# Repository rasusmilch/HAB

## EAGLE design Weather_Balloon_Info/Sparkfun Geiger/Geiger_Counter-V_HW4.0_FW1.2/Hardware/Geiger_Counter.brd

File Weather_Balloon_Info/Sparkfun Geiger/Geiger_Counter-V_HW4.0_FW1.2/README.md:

Geiger Counter
========================================
[
*Geiger Counter (SEN-11345)*](https://www.sparkfun.com/products/11345)

This USB powered Geiger Counter is equipped with an ATMega328 that can be programmed in-circuit. Out of the box, the board works
at 9600 bps over any serial terminal and generates random bits in reaction to background radiation.

Repository Contents
-------------------
* **/Firmware** - Firmware that ships on the Geiger Counter
* **/Hardware** - All Eagle design files (.brd, .sch)
* **/Production** - Test bed files and production panel files

Product Versions
----------------
* [SEN-11345](https://www.sparkfun.com/products/11345)- Version 2.1. Current.
* [SEN-10742](https://www.sparkfun.com/products/retired/10742)- Version 1.2-Retired. 

Version History
---------------
* [v21](https://github.com/sparkfun/Geiger_Counter/tree/HW_2.1_FW_2.1) GitHub version 2.1 files.
* [v12](https://github.com/sparkfun/Geiger_Counter/tree/v12) GitHub version 1.2 files. 

License Information
-------------------
The hardware is released under [Creative Commons ShareAlike 4.0 International](https://creativecommons.org/licenses/by-sa/4.0/).
The code is beerware; if you see me (or any other SparkFun employee) at the local, and you've found our code helpful, please buy us a round!

Distributed as-is; no warranty is given.

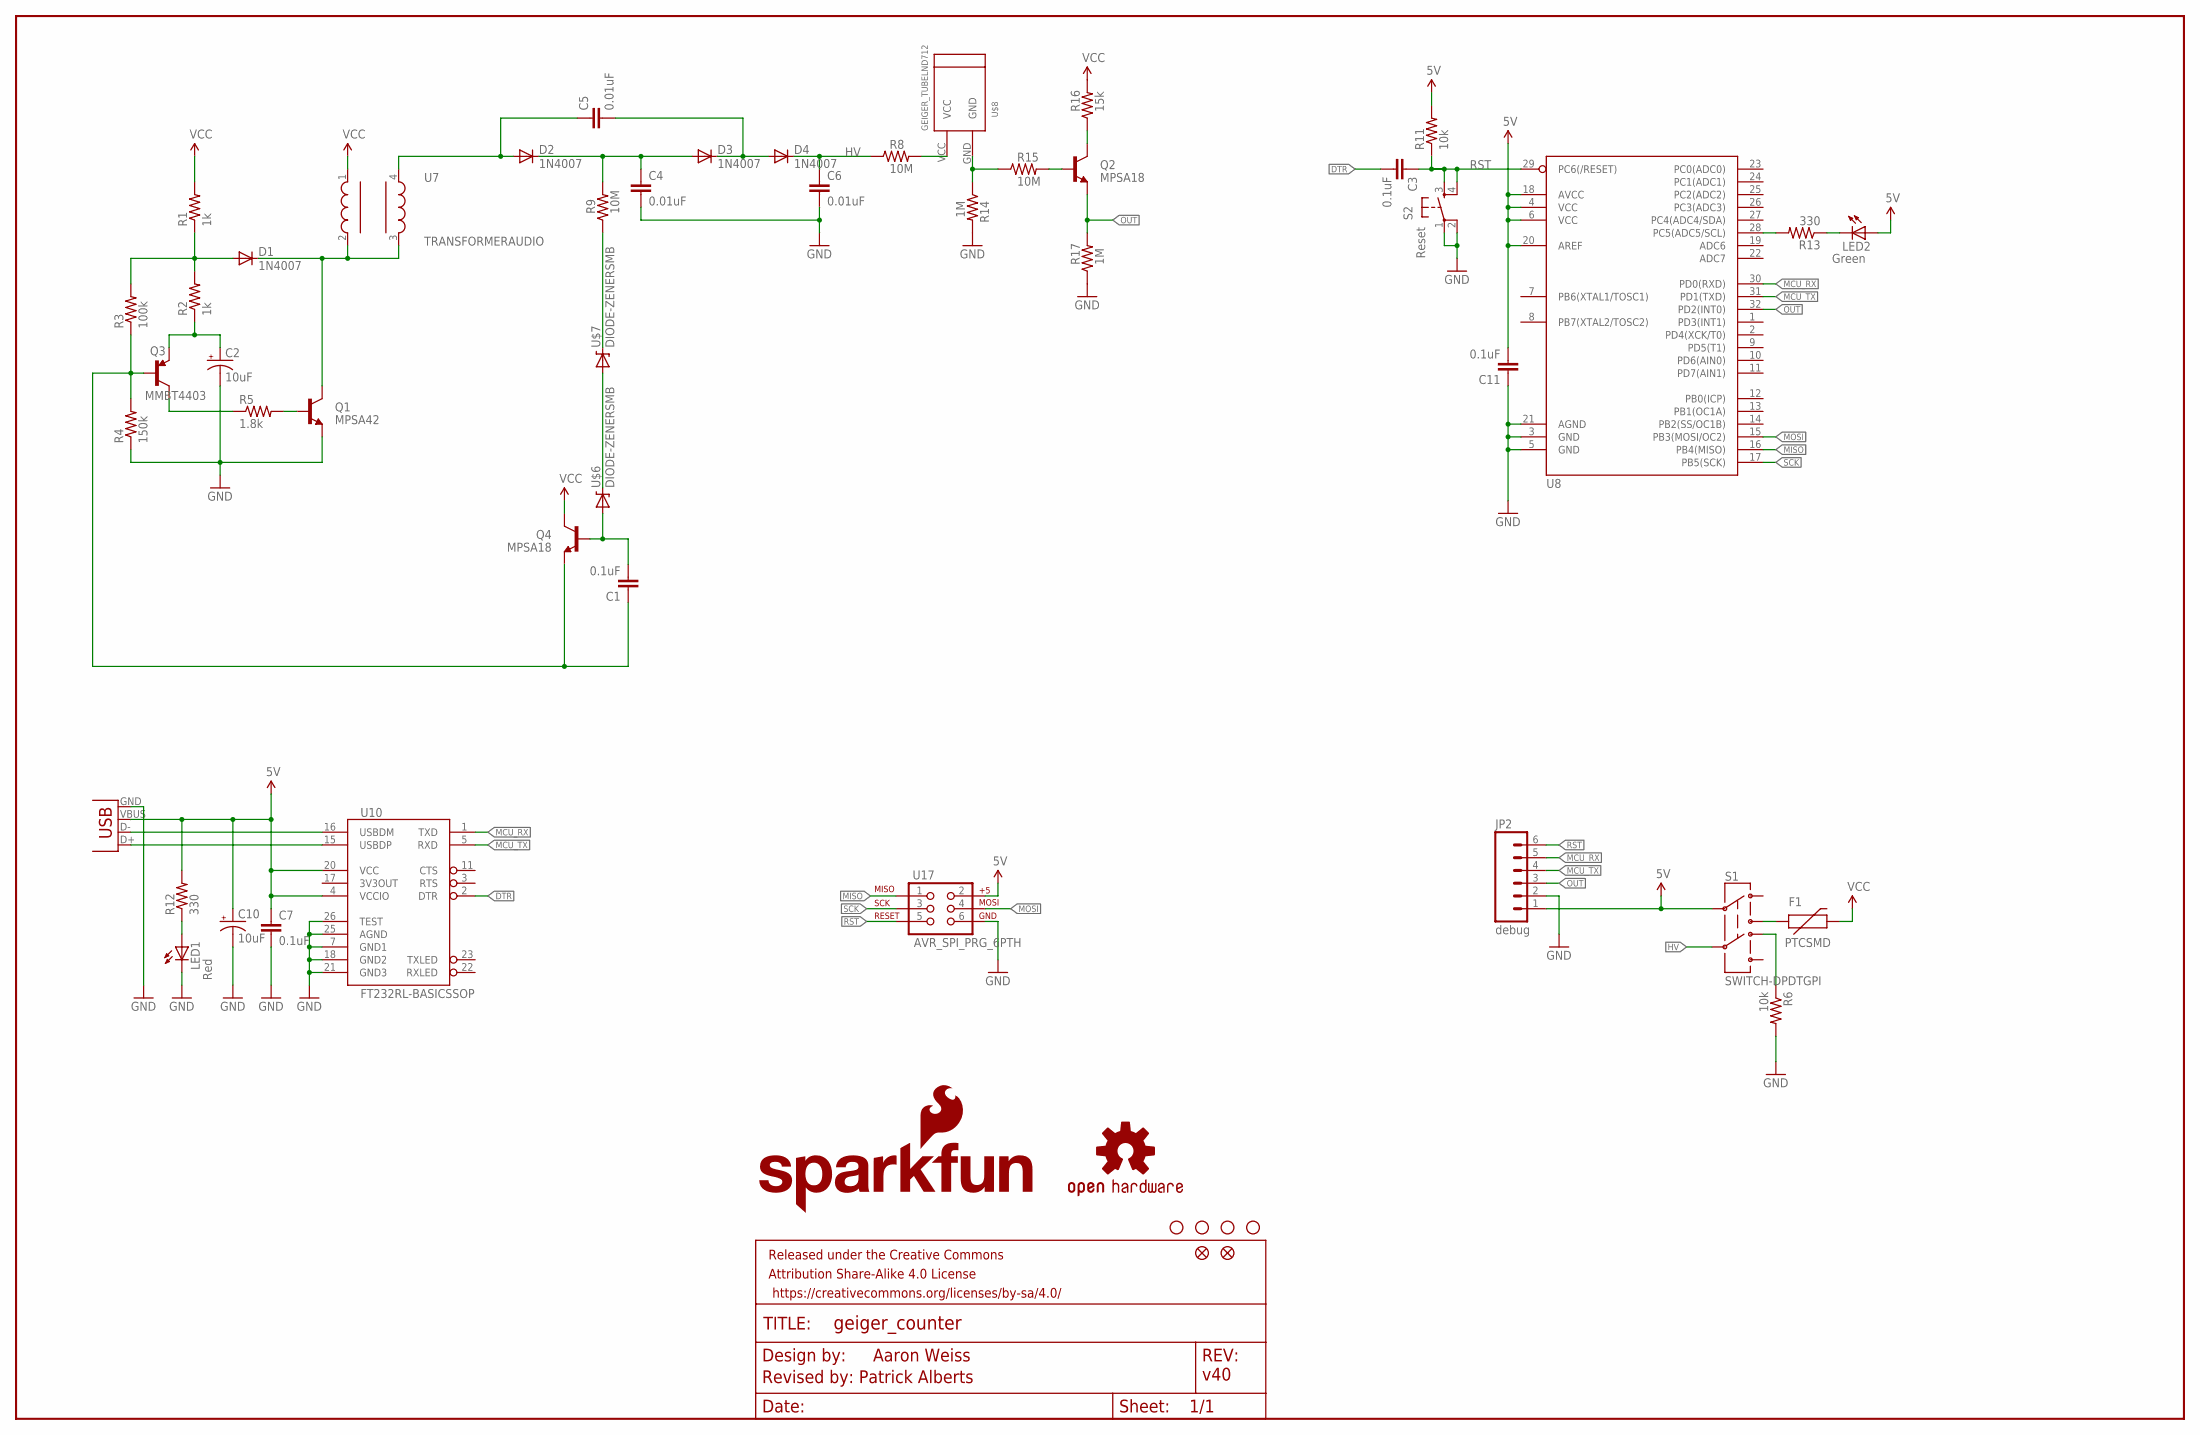
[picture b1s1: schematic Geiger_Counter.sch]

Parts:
C1, C3, C7, C11: 0.1uF; 0603-CAP
C2, C10: 10uF; EIA3216
C4, C5, C6: 0.01uF; CAP-PTH-LARGE
D1: 1N4007; DIODE-HV
D2, D3, D4: 1N4007; DIODE-1N4001
F1: PTCSMD; PTC-1206
FID1, FID2: FIDUCIAL1X2; FIDUCIAL-1X2
FRAME2: FRAME-LEDGER; CREATIVE_COMMONS
JP2: debug; 1X06
LED1: Red; LED-1206
LED2: Green; LED-1206
LOGO1: OSHW-LOGOM; OSHW-LOGO-M
LOGO2: SFE_LOGO_NAME_FLAME.1_INCH; SFE_LOGO_NAME_FLAME_.1
Q1: MPSA42; SOT23-3
Q2, Q4: MPSA18; TO-92
Q3: MMBT4403; SOT23-3
R1, R2: 1k; 0603-RES
R3: 100k; 0603-RES
R4: 150k; 0603-RES
R5: 1.8k; 0603-RES
R6: 10k; AXIAL-0.3
R8, R9, R15: 10M; AXIAL-0.3
R11: 10k; 0603-RES
R12: 330; 0603
R13: 330; 0603-RES
R14, R17: 1M; AXIAL-0.3
R16: 15k; AXIAL-0.3
S1: SWITCH-DPDTGPI; GPI-152-3013
S2: Reset; TACTILE_SWITCH_SMD
U7: TRANSFORMERAUDIO; TRANSFORMER
U8: ATMEGA328_SMT; TQFP32-08
U10: FT232RL-BASICSSOP; SSOP28DB
U17: AVR_SPI_PRG_6PTH; 2X3
U$1, U$2, U$3, U$4: STAND-OFF
U$6, U$7: DIODE-ZENERSMB; SMB-DIODE
U$8: GEIGER_TUBELND712; GEIGER_TUBE
X1: USBSMD; USB-MINIB

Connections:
5V: C7.1, C10.A (+), C11.2, JP2.1, LED2.A, R11.2, R12.2, S1.C@1 (2), U8.4 (VCC), U8.6 (VCC), U8.18 (AVCC), U8.20 (AREF), U10.4 (VCCIO), U10.20 (VCC), U17.2, X1.VBUS
DTR: C3.2, U10.2 (DTR)
GND: C2.C (-), C4.2, C6.2, C10.C (-), C11.1, JP2.2, LED1.C, Q1.2 (E), R4.1, R6.P$2 (2), R14.P$2 (2), R17.P$1 (1), S2.1, S2.2, U8.3 (GND), U8.5 (GND), U8.21 (AGND), U10.7 (GND1), U10.18 (GND2), U10.21 (GND3), U10.25 (AGND), U10.26 (TEST), U17.6, X1.GND
HV: C6.1, D4.C, R8.P$1 (1), S1.C@2 (5)
MCU_RX: JP2.5, U8.30 (PD0(RXD)), U10.1 (TXD)
MCU_TX: JP2.4, U8.31 (PD1(TXD)), U10.5 (RXD)
MISO: U8.16 (PB4(MISO)), U17.1
MOSI: U8.15 (PB3(MOSI/OC2)), U17.4
unnamed: F1.1, S1.20 (3)
unnamed: D1.A, R1.1, R2.2, R3.2
unnamed: R14.P$1 (1), R15.P$1 (1), U$8.GND
unnamed: C2.A (+), Q3.2 (E), R2.1
unnamed: Q2.2 (B), R15.P$2 (2)
unnamed: Q3.3 (C), R5.1
unnamed: R6.P$1 (1), S1.11 (4)
unnamed: Q2.3 (C), R16.P$1 (1)
unnamed: Q1.1 (B), R5.2
unnamed: D1.C, Q1.3 (C), U7.2, U7.3
unnamed: C4.1, D2.C, D3.A, R9.P$2 (2)
unnamed: C5.2, D3.C, D4.A
unnamed: R8.P$2 (2), U$8.VCC
unnamed: U10.16 (USBDM), X1.D-
unnamed: U10.15 (USBDP), X1.D+
unnamed: R9.P$1 (1), U$7.C
unnamed: LED1.A, R12.1
unnamed: LED2.C, R13.1
unnamed: R13.2, U8.28 (PC5(ADC5/SCL))
unnamed: U$6.C, U$7.A
unnamed: C1.2, Q4.2 (B), U$6.A
OSC1: C5.1, D2.A, U7.4
OSC2: C1.1, Q3.1 (B), Q4.1 (E), R3.1, R4.2
OUT: JP2.3, Q2.1 (E), R17.P$2 (2), U8.32 (PD2(INT0))
RST: C3.1, JP2.6, R11.1, S2.3, S2.4, U8.29 (PC6(/RESET)), U17.5
SCK: U8.17 (PB5(SCK)), U17.3
VCC: F1.2, Q4.3 (C), R1.2, R16.P$2 (2), U7.1

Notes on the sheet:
Aaron Weiss
Revised by: Patrick Alberts
v40

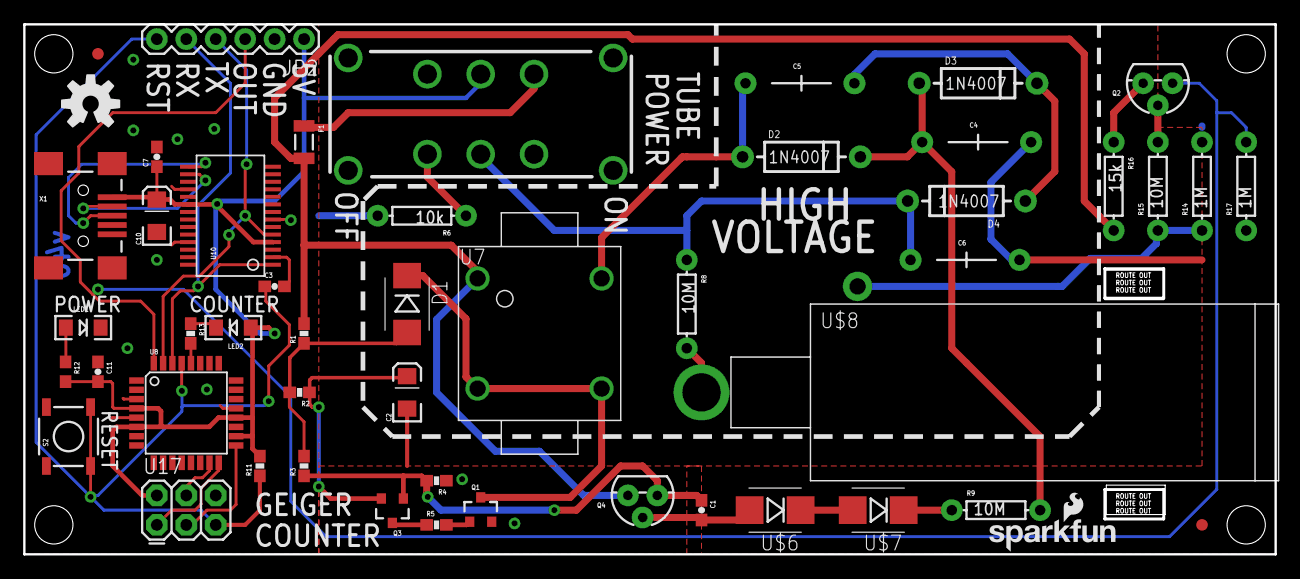
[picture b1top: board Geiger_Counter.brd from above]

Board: 2 copper layers, 107.9 x 45.7 mm, 55 parts (0 on the bottom side), 35 nets.

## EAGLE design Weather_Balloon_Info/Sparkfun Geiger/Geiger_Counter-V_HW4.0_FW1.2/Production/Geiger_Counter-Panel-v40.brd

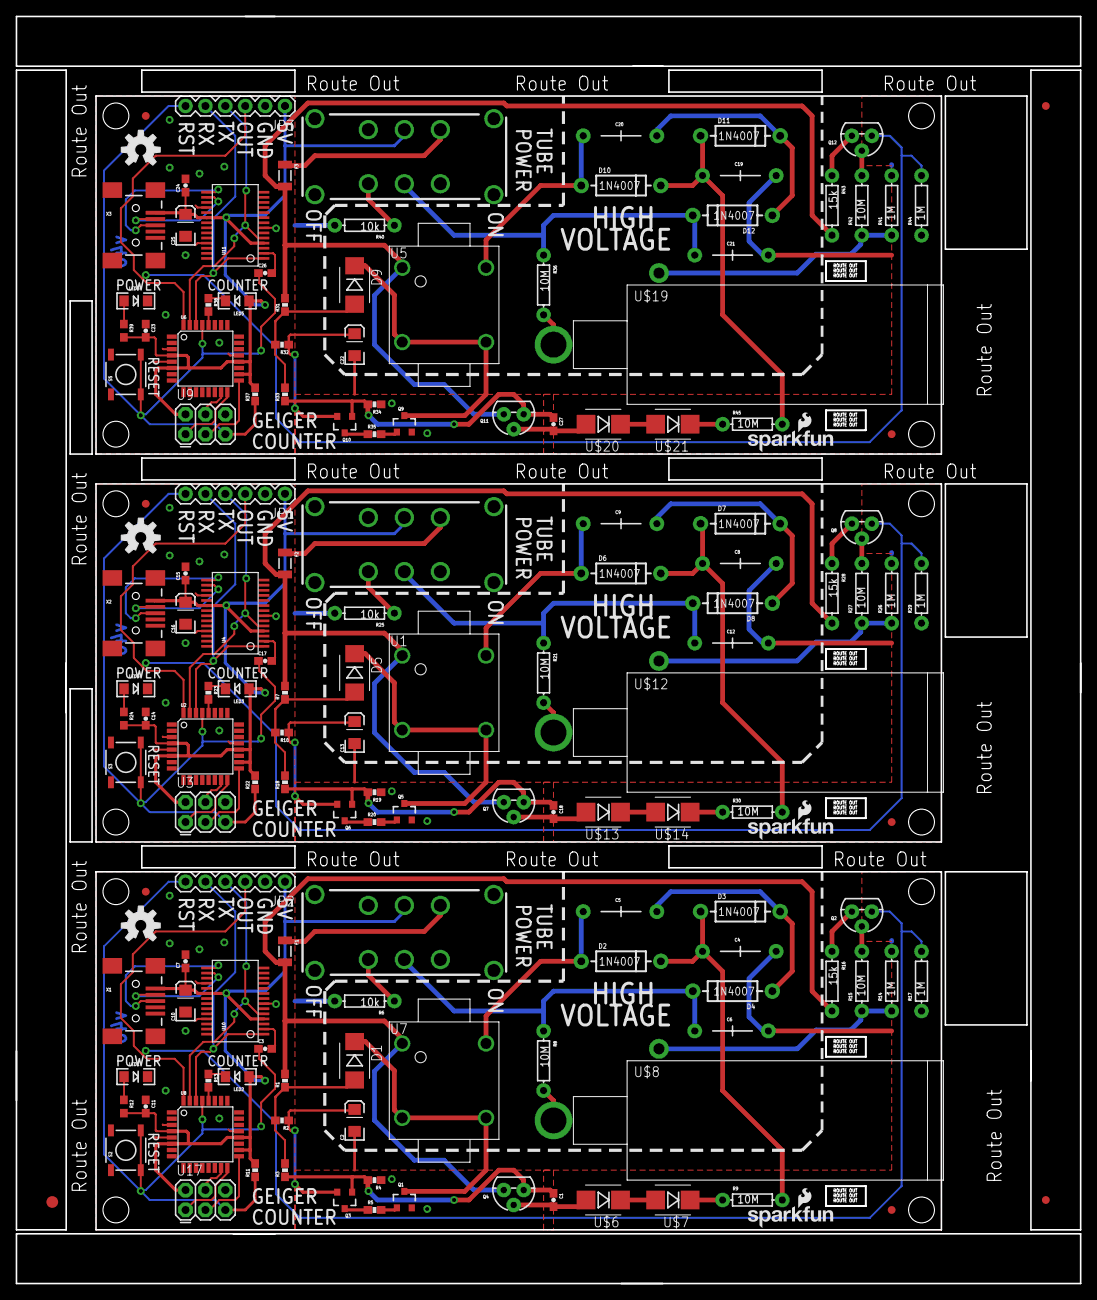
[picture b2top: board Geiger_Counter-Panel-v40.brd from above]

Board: 2 copper layers, 135.8 x 161.7 mm, 165 parts (0 on the bottom side), 105 nets.

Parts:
C1, C3, C7, C11, C14, C15, C17, C18, C23, C24, C26, C27: 0.1uF; 0603-CAP
C2, C10, C13, C16, C22, C25: 10uF; EIA3216
C4, C5, C6, C8, C9, C12, C19, C20, C21: 0.01uF; CAP-PTH-LARGE
D1, D5, D9: 1N4007; DIODE-HV
D2, D3, D4, D6, D7, D8, D10, D11, D12: 1N4007; DIODE-1N4001
E$1: FIDUCIAL-1.5X3
E$2, E$3: FIDUCIAL-1X2
F1, F2, F3: PTCSMD; PTC-1206
FID1, FID2, FID3, FID4, FID5, FID6: FIDUCIAL1X2; FIDUCIAL-1X2
JP1, JP2, JP3: debug; 1X06
LED1, LED4, LED6: Red; LED-1206
LED2, LED3, LED5: Green; LED-1206
LOGO1, LOGO3, LOGO5: OSHW-LOGOM; OSHW-LOGO-M
LOGO2, LOGO4, LOGO6: SFE_LOGO_NAME_FLAME.1_INCH; SFE_LOGO_NAME_FLAME_.1
Q1, Q5, Q9: MPSA42; SOT23-3
Q2, Q4, Q7, Q8, Q11, Q12: MPSA18; TO-92
Q3, Q6, Q10: MMBT4403; SOT23-3
R1, R2, R7, R10, R31, R32: 1k; 0603-RES
R3, R18, R33: 100k; 0603-RES
R4, R19, R34: 150k; 0603-RES
R5, R20, R35: 1.8k; 0603-RES
R6, R25, R40: 10k; AXIAL-0.3
R8, R9, R15, R21, R27, R30, R36, R42, R45: 10M; AXIAL-0.3
R11, R22, R37: 10k; 0603-RES
R12, R24, R39: 330; 0603
R13, R23, R38: 330; 0603-RES
R14, R17, R26, R29, R41, R44: 1M; AXIAL-0.3
R16, R28, R43: 15k; AXIAL-0.3
S1, S4, S6: SWITCH-DPDTGPI; GPI-152-3013
S2, S3, S5: Reset; TACTILE_SWITCH_SMD
U1, U5, U7: TRANSFORMERAUDIO; TRANSFORMER
U2, U6, U8: TQFP32-08
U3, U9, U17: AVR_SPI_PRG_6PTH; 2X3
U4, U10, U11: FT232RL-BASICSSOP; SSOP28DB
U$1, U$2, U$3, U$4, U$5, U$9, U$10, U$11, U$15, U$16, U$17, U$18: STAND-OFF
U$6, U$7, U$13, U$14, U$20, U$21: DIODE-ZENERSMB; SMB-DIODE
U$8, U$12, U$19: GEIGER_TUBELND712; GEIGER_TUBE
X1, X2, X3: USBSMD; USB-MINIB

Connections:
5V: C7.1, C10.A, C11.2, JP2.1, LED2.A, R11.2, R12.2, S1.C@1, U8.4, U8.6, U8.18, U8.20, U10.4, U10.20, U17.2, X1.VBUS
5V1: C14.2, C15.1, C16.A, JP1.1, LED3.A, R22.2, R24.2, S4.C@1, U2.4, U2.6, U2.18, U2.20, U3.2, U4.4, U4.20, X2.VBUS
5V2: C23.2, C24.1, C25.A, JP3.1, LED5.A, R37.2, R39.2, S6.C@1, U6.4, U6.6, U6.18, U6.20, U9.2, U11.4, U11.20, X3.VBUS
DTR: C3.2, U10.2
DTR1: C17.2, U4.2
DTR2: C26.2, U11.2
GND: C2.C, C4.2, C6.2, C10.C, C11.1, JP2.2, LED1.C, Q1.2, R4.1, R6.P$2, R14.P$2, R17.P$1, S2.1, S2.2, U8.3, U8.5, U8.21, U10.7, U10.18, U10.21, U10.25, U10.26, U17.6, X1.GND
GND1: C8.2, C12.2, C13.C, C14.1, C16.C, JP1.2, LED4.C, Q5.2, R19.1, R25.P$2, R26.P$2, R29.P$1, S3.1, S3.2, U2.3, U2.5, U2.21, U3.6, U4.7, U4.18, U4.21, U4.25, U4.26, X2.GND
GND2: C19.2, C21.2, C22.C, C23.1, C25.C, JP3.2, LED6.C, Q9.2, R34.1, R40.P$2, R41.P$2, R44.P$1, S5.1, S5.2, U6.3, U6.5, U6.21, U9.6, U11.7, U11.18, U11.21, U11.25, U11.26, X3.GND
HV: C6.1, D4.C, R8.P$1, S1.C@2
HV1: C12.1, D8.C, R21.P$1, S4.C@2
HV2: C21.1, D12.C, R36.P$1, S6.C@2
MCU_RX: JP2.5, U8.30, U10.1
MCU_RX1: JP1.5, U2.30, U4.1
MCU_RX2: JP3.5, U6.30, U11.1
MCU_TX: JP2.4, U8.31, U10.5
MCU_TX1: JP1.4, U2.31, U4.5
MCU_TX2: JP3.4, U6.31, U11.5
MISO: U8.16, U17.1
MISO1: U2.16, U3.1
MISO2: U6.16, U9.1
MOSI: U8.15, U17.4
MOSI1: U2.15, U3.4
MOSI2: U6.15, U9.4
unnamed: F1.1, S1.20
unnamed: D1.A, R1.1, R2.2, R3.2
unnamed: R14.P$1, R15.P$1, U$8.GND
unnamed: C2.A, Q3.2, R2.1
unnamed: Q2.2, R15.P$2
unnamed: Q3.3, R5.1
unnamed: R6.P$1, S1.11
unnamed: Q2.3, R16.P$1
unnamed: Q1.1, R5.2
unnamed: D1.C, Q1.3, U7.2, U7.3
unnamed: C4.1, D2.C, D3.A, R9.P$2
unnamed: C5.2, D3.C, D4.A
unnamed: R8.P$2, U$8.VCC
unnamed: U10.16, X1.D-
unnamed: D5.A, R7.1, R10.2, R18.2
unnamed: U10.15, X1.D+
unnamed: R9.P$1, U$7.C
unnamed: LED1.A, R12.1
unnamed: LED2.C, R13.1
unnamed: R13.2, U8.28
unnamed: U$6.C, U$7.A
unnamed: C1.2, Q4.2, U$6.A
unnamed: C13.A, Q6.2, R10.1
unnamed: Q6.3, R20.1
unnamed: Q5.1, R20.2
unnamed: D5.C, Q5.3, U1.2, U1.3
unnamed: C8.1, D6.C, D7.A, R30.P$2
unnamed: C9.2, D7.C, D8.A
unnamed: R21.P$2, U$12.VCC
unnamed: LED3.C, R23.1
unnamed: R23.2, U2.28
unnamed: U4.16, X2.D-
unnamed: U4.15, X2.D+
unnamed: LED4.A, R24.1
unnamed: R25.P$1, S4.11
unnamed: F2.1, S4.20
unnamed: R26.P$1, R27.P$1, U$12.GND
unnamed: Q8.2, R27.P$2
unnamed: Q8.3, R28.P$1
unnamed: R30.P$1, U$14.C
unnamed: U$13.C, U$14.A
unnamed: C18.2, Q7.2, U$13.A
unnamed: D9.A, R31.1, R32.2, R33.2
unnamed: C22.A, Q10.2, R32.1
unnamed: Q10.3, R35.1
unnamed: Q9.1, R35.2
unnamed: D9.C, Q9.3, U5.2, U5.3
unnamed: C19.1, D10.C, D11.A, R45.P$2
unnamed: C20.2, D11.C, D12.A
unnamed: R36.P$2, U$19.VCC
unnamed: LED5.C, R38.1
unnamed: R38.2, U6.28
unnamed: U11.16, X3.D-
unnamed: U11.15, X3.D+
unnamed: LED6.A, R39.1
unnamed: R40.P$1, S6.11
unnamed: F3.1, S6.20
unnamed: R41.P$1, R42.P$1, U$19.GND
unnamed: Q12.2, R42.P$2
unnamed: Q12.3, R43.P$1
unnamed: R45.P$1, U$21.C
unnamed: U$20.C, U$21.A
unnamed: C27.2, Q11.2, U$20.A
OSC1: C5.1, D2.A, U7.4
OSC2: C1.1, Q3.1, Q4.1, R3.1, R4.2
OSC3: C9.1, D6.A, U1.4
OSC4: C18.1, Q6.1, Q7.1, R18.1, R19.2
OSC5: C20.1, D10.A, U5.4
OSC6: C27.1, Q10.1, Q11.1, R33.1, R34.2
OUT: JP2.3, Q2.1, R17.P$2, U8.32
OUT1: JP1.3, Q8.1, R29.P$2, U2.32
OUT2: JP3.3, Q12.1, R44.P$2, U6.32
RST: C3.1, JP2.6, R11.1, S2.3, S2.4, U8.29, U17.5
RST1: C17.1, JP1.6, R22.1, S3.3, S3.4, U2.29, U3.5
RST2: C26.1, JP3.6, R37.1, S5.3, S5.4, U6.29, U9.5
SCK: U8.17, U17.3
SCK1: U2.17, U3.3
SCK2: U6.17, U9.3
VCC: F1.2, Q4.3, R1.2, R16.P$2, U7.1
VCC1: F2.2, Q7.3, R7.2, R28.P$2, U1.1
VCC2: F3.2, Q11.3, R31.2, R43.P$2, U5.1

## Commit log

2016-09-10 Beeper working. Magnetometer and 18B20.
2016-09-11 Added accelerometer and non-blocking DS18B20 temperature conversion
2016-09-16 Refactored to use generic Makefile instead of Arduino IDE. Allowing external IDE and more traditional Cpp
2016-09-18 Progress on new sensors, fuel gauge.
2016-09-20 Restructured sensor data. GPS works.
2016-09-20 Calibration of accel, mag and gyro.
2016-09-21 Geiger count ISR and reorganize sensor configs. New sensor found struct.
2016-09-25 Logging packed
2016-09-27 Initial PCB design with throughhole components. Layout not finilized.
2016-09-29 Before manual trace width adjust
2016-10-01 Reorganized folder structure
2016-10-01 Restructured folders to move board level files to board directory.
2016-10-02 Updated PCB board for larger traces and more compact design.
2016-10-11 PID control and beginning of altitude alarm.
2016-10-12 Prototype pre-assembly with debugging enabled
2016-10-13 Launch code finalized.
2016-10-14 Added SDCard CSV dump function and some serial commands. Untested.
2016-10-14 After flight data retrieval
2016-10-15 Investigated serial command read failure on atmega328p. Found nothing. Added pressure calculation to set altitude command.
2016-11-07 Update before move to github
2016-11-07 Early rough draft of the Design Document
2016-11-09 Updated board schematic and layout files to remove title block and page outline for presentation.
2016-11-10 Design document rev 1.0

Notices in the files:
parts and their libraries:
SparkFun-DiscreteSemi: Licensing: CC v3.0 Share-Alike You are welcome to use this library for commercial purposes.
SparkFun-Resistors: Licensing: Creative Commons ShareAlike 4.0 International - https://creativecommons.org/licenses/by-sa/4.0
SparkFun-Aesthetics: Released under the Creative Commons
